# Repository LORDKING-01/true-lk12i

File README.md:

# LK12I-H
Harmonized PISO/SIPO version of the LK12I Protocol

# Description
The LK12I-H protocol is a modular, overclockable extension hub for the purposes of tinkering and programming. The main functionalities is the reading and writing of binary data from and to header pins on the Circuit Board.

# Context for new tinkerers

## Data, Bytes and Bits
Data refers to information. In the electrical scene, one of the types of data we can store is known as binary, or 1s and 0s, and ONs and OFFs. 1s are associated with HIGH signals (the signal coming from your power source) and 0s are associated with LOW signals (the signal going to ground). 1s and 0s are referred to as 'Bits', which just means a singular bit of binary data. A byte, on the other hand, is a collection of 8 bits in a specific order. Bytes allow us to organize our information in a standard format. When something outputs data at multiple sources, we list the sources with Qx, where x is a zero-based index. For example, the first output would be called Q0 while the second would be called Q1. When something takes in multiple data, we name the inputs in alphabetical order, such as ABC and D.

## Serial Data
Serial data refers to binary bits sent in sequence, one after each other, in order. A common example of serial data is data sent to and from your USB port or the music sent to your headphones from your phone. The major advantage is that it requires much less input/output ports, but the major disadvantage is that it is slower. A good analogy for serial data is to imagine adding up numbers you hear your friend saying.

## Parallel Data
Parallel data refers to binary bits sent simultaneously. A common example is the the individual data pins in an USB port. Be mindful that serial data can be transmitted in parallel. A good analogy for parallel data is to imagine adding numbers where you can see all of them on a sheet of paper.

## Clock
In electronics, a clock refers to a periodic cycle of HIGH and LOW signals. Many components use clocks to synchronize their procedures within the component or with other components. In most cases, components activate on a clock's rising edge, which is the exact point that the signal changes from LOW to HIGH.

## SIPO
Stands for Serial-In, Parallel-Out. It is essentially a translator that can take serial data as bytes (packages of data) to transmit each bit of that byte in parallel (simultaneously). Think of it as listening to your friend telling you which numbers they want you to write verbally while you write it down on paper. Your friend's voice is the serial data while the finished paper is the parallel data. 

## PISO
Stands for Parallel-In, Serial-Out. It is essentially the opposite of the SIPO. It takes in information from multiple sources and packages them as serial data. Imagine reading numbers on a piece of paper to your friend. The paper has all the information laid out to you in parallel, simultaneously. However, it is up to you to tell your friend the numbers in order, which represents serial data.

## Shift Registers
Shift registers, in essence, refer to components that can store data temporarily while we collect it. The shift registers used in this repo is the 74x595 SIPO shift register and the 74x165 PISO shift register.

### 74x595 SIPO Shift Register
The 74x595 is the component we will utilize to send our data to multiple recievers in this project. Please refer to the pinout.

As stated before, Q0 to Q7 is our list of outputs. Pin 14, or SER, is the serial data pin we will use to send bytes that the 595 can translate and output. Pin 13 is an Active-LOW Output Enable pin. This means that if we tie it to ground, our outputs will be available.  RCLK and SCLK are two clock inputs that will be explained later. Pin 10 is another Active-LOW pin which resets the chip if it is tied to ground. To counteract that, we tie it to our source voltage. We have two different clocks made available to us, Register Clock and Shift Clock. When detecting a rising edge, it moves every Q output to the next Q output. That would mean that the data in our Q0 would go to Q1, and our Q1 data would already be at Q2 at that point. When the register clock outputs a high edge, the outputs are updated to the current value they store. Usually, the shift clock is pulsed 8 times before the register clock pulses to correctly map the bits in the right orientation. In order to imagine this, it may help to imagine 8 workers in a factory line. The first person in the line is an expert at operating red items, while the second person in the line is an expert at operating orange items. After they operate on their items, the shift clock is pulsed 8 times, which moves the items down 8 spaces. Shortly after the eighth item follows a cardboard box that keeps shifting down until it hits the eighth person. Finally, after everyone has a cardboard box, the register clock pulses, and the workers are allowed to open their box, revealing the item they are an expert at operating on.

###
The 74x165 is the component we will utilize to package our parallel data in a serial manner. Please refer to the pinout.

The centre 4 pins on either side are the input pins. Thankfully, they are in a relatively sensible order. Think of the 165 as the inverse of the 595. The CLK INH, or Clock Inhibit, is tied to ground. The clock pin recieves the clock inputs as normal. The Load pin essentially allows us to update our inputs. It is the opposite of the register clock on the 595. As an analogy, the LOAD pin lets each pin collect carboard boxes when it is pulled LOW, and it gives it to the workers when it is pulled HIGH. The last shift, or Q7, functions as the chip's output. It matches whatever the eighth worker has inside their box. As the clock pulses, the cardboard boxes shift one spot down the assembly line, which exposes new boxes to the Q7 pin. After all the boxes are collected by the serial data pin, we can load the belt with new boxes. It is important to understand that we need to read the clock pin for the 165 to synchronize it with when we see what is inside each box.

## The Phase Shift Issue
To trigger the latch, a 4017 was used to essentially pulse once after each byte was completed to tell our 595's latch to pulse. However, on startup, there are some instances where the 4017's byte sequence is not synchronized with the byte sent by the Arduino. As a fix to preserve Arduino pins, a 'Phase Shift' mechanism was added to the main branch. It essentially works as a manual override to synchronize bytes. To use this feature, it is recommended to send a byte where Q0 is on and the rest off (For this repository, A-H and Q-0 are mapped in the order of most significant byte first for ease of reading and access, but can be easily changed). It is recommended to have LEDs running in parallel to the loads placed on your 595 as a source of indication. Of course, this means that your overall amperage for the 595 is lower, but loads shouldn't be running straight off the 595 anyway if it is inductive or a current monster. After the byte is sent, send + or - to shift the order of the byte until it reaches Q0. Alternatively, you can just place an indicator load (like an LED) on Q0 for calibration. This phase shift is saved to memory, so ideally, it should boot up calibrated. If it doesn't, recalibrate.

# Branches

## LK12I-H
The LK12I-H (lordking12 Interface, harmonized) is the most complete and stable version of the LK12I protocol. It features both the SIPO and PISO functionalities, packaged with working code to use them simultaneously. The code can be rewritten to a header and library for easier, cleaner access. The main drawback of the stability is lower serial communication rates and noticeably high-latency update speeds. However, the code is slightly blocking and is not ideal for high-speed data transfer such as for a high-speed Bluetooth port.

## LK12I-HvOC
The LK12I-HvOC(lordking12 Interface, Harmonized Overclock version, or HAVOC) is the fastest running, mostly stable release of the LK12I-H protocol. The serial port is ran at 250000 baud for the fastest, least blocking code.

## LK12I-HvOC-5x3 (Unreleased, Experimental)
The LK12I-HvOC-5x3 is an experimental prerelease that utilizes a 555/556 timer for overclocking on the client-side. This project is most ideal with the CMOS variants of the 4017, 74x165, 555, and 74x595.

## LK12I-SIPO
The LK12I protocol with only the SIPO functionalities.

## LK12I-PISO
The LK12I protocol with only the PISO functionalities.

# To-do
Make the Lk12I-h daisy-chainable

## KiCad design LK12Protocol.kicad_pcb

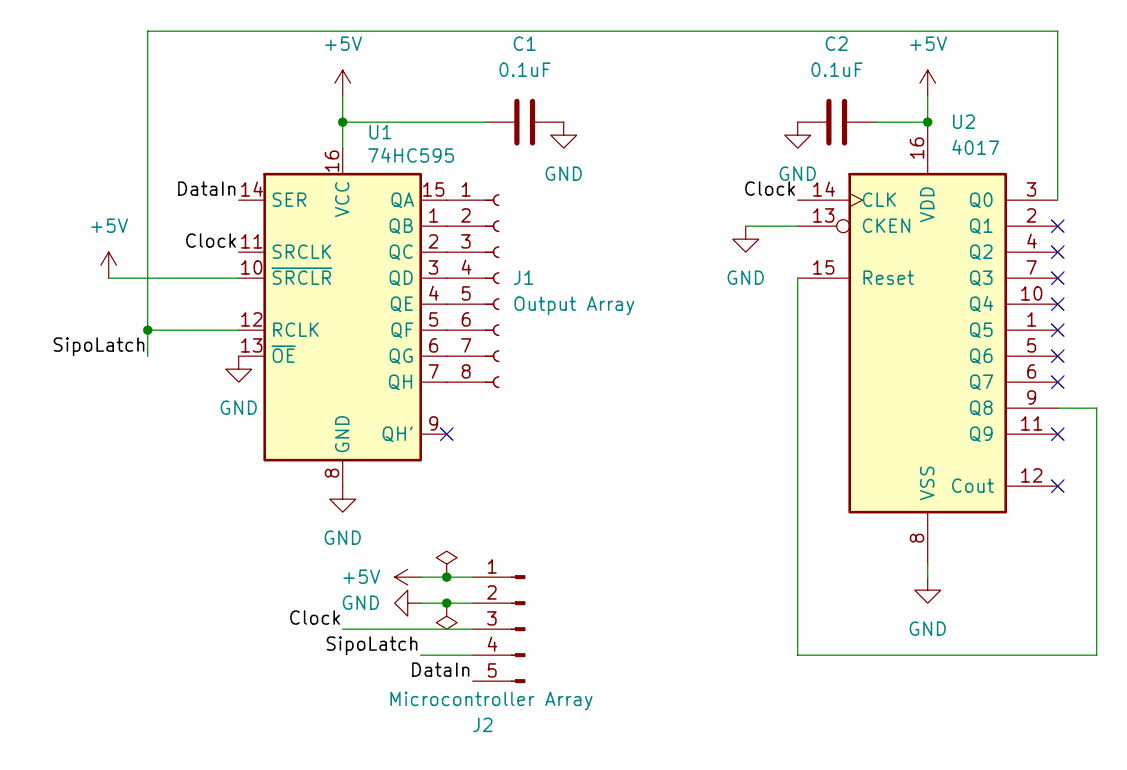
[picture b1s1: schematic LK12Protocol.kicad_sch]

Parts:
C1, C2: 0.1uF; CP_Radial_D4.0mm_P1.50mm
J1: Output Array; PinSocket_1x08_P2.54mm_Horizontal
J2: Microcontroller Array; PinHeader_1x05_P2.54mm_Horizontal
U1: 74HC595; DIP-16_W7.62mm
U2: 4017; DIP-16_W7.62mm

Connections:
+5V: C1.1, C2.2, J2.1, U1.10 (~SRCLR), U1.16 (VCC), U2.16 (VDD)
/Clock: J2.3, U1.11 (SRCLK), U2.14 (CLK)
/DataIn: J2.5, U1.14 (SER)
/SipoLatch: J2.4, U1.12 (RCLK), U2.3 (Q0)
GND: C1.2, C2.1, J2.2, U1.8 (GND), U1.13 (~OE), U2.8 (VSS), U2.13 (CKEN)
unnamed: J1.1, U1.15 (QA)
unnamed: J1.2, U1.1 (QB)
unnamed: J1.3, U1.2 (QC)
unnamed: J1.4, U1.3 (QD)
unnamed: J1.5, U1.4 (QE)
unnamed: J1.6, U1.5 (QF)
unnamed: J1.7, U1.6 (QG)
unnamed: J1.8, U1.7 (QH)
unnamed: U2.9 (Q8), U2.15 (Reset)

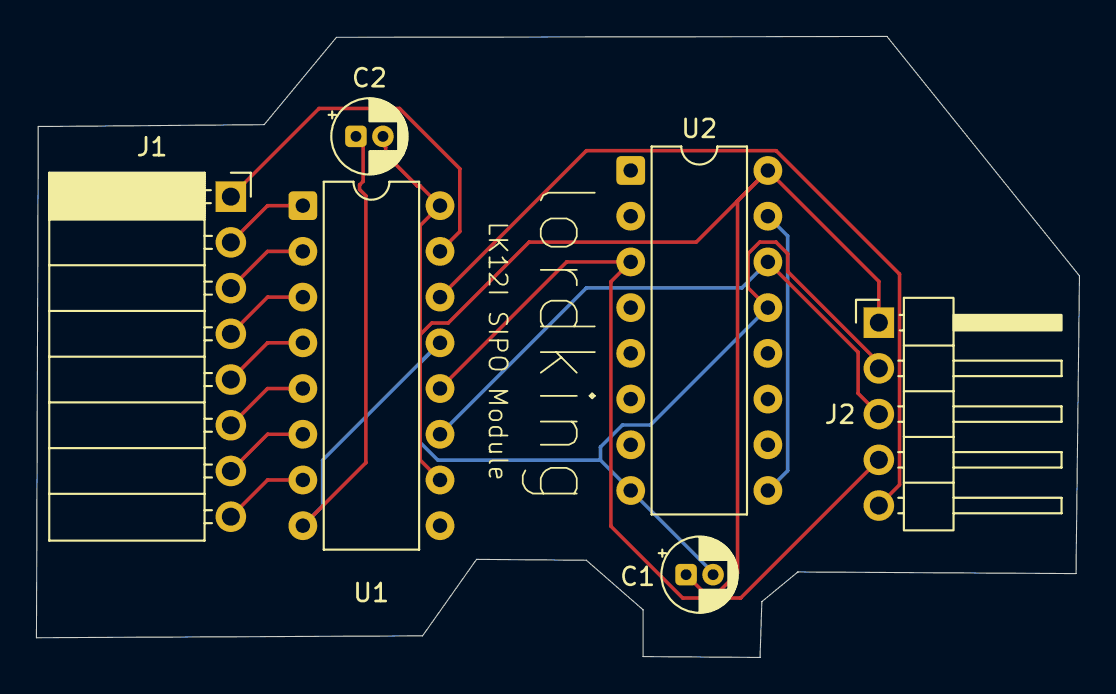
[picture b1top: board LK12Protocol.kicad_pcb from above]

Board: 2 copper layers, 57.9 x 34.5 mm, 6 parts (0 on the bottom side), 14 nets.
